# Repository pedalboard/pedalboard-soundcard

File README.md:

# Pedalboard Soundcard

I²S audio codec HAT for Raspberry Pi — ADC + DAC for the [Open Pedalboard](https://github.com/pedalboard) system.

**[Documentation →](https://pedalboard.github.io/pedalboard-soundcard/latest/)**

## Features

- TI Burr-Brown PCM1863 ADC (106dB SNR) + PCM5242 DAC (112dB SNR)
- Stereo differential input (guitar) + stereo output (amp)
- I²S interface to Raspberry Pi GPIO header
- Low-latency audio path for real-time effects
- Raspberry Pi HAT form factor

## Links

- [Interactive schematic & PCB viewer](https://pedalboard.github.io/pedalboard-soundcard/latest/board/)
- [Digi-Key shared list](https://www.digikey.ch/de/mylists/list/OT2O5ZLS9K)

## Development Setup

### Prerequisites

- [KiCad](https://www.kicad.org/) 10+
- [KiKit](https://github.com/yaqwsx/KiKit) (panelization)
- [mise](https://mise.jdx.dev/) (environment management)

### Environment

The schematic references KiKit's symbol and footprint libraries via the `${KIKIT_LIB}` environment variable. This is set per-machine using a `mise.local.toml` file (gitignored).

After cloning, create `mise.local.toml` in the project root:

```toml
[env]
KIKIT_LIB = "/path/to/kikit/resources"
```

Find your KiKit resources path with:

```sh
python3 -c "import kikit, os; print(os.path.join(os.path.dirname(kikit.__file__), 'resources'))"
```

Then trust the config:

```sh
mise trust mise.local.toml
```

### Checks

Run ERC and DRC:

```sh
make test
```

## Acknowledgements

Based on Dave Vandenbout's [RPi Hat Template](https://github.com/devbisme/RPi_Hat_Template).
Schematics derived from Jośe Fernando Moyano's [ZynADC](https://github.com/zynthian/zynthian-hw/tree/master/ZynADAC) ([CC BY-SA 4.0](https://creativecommons.org/licenses/by-sa/4.0/)).

## License

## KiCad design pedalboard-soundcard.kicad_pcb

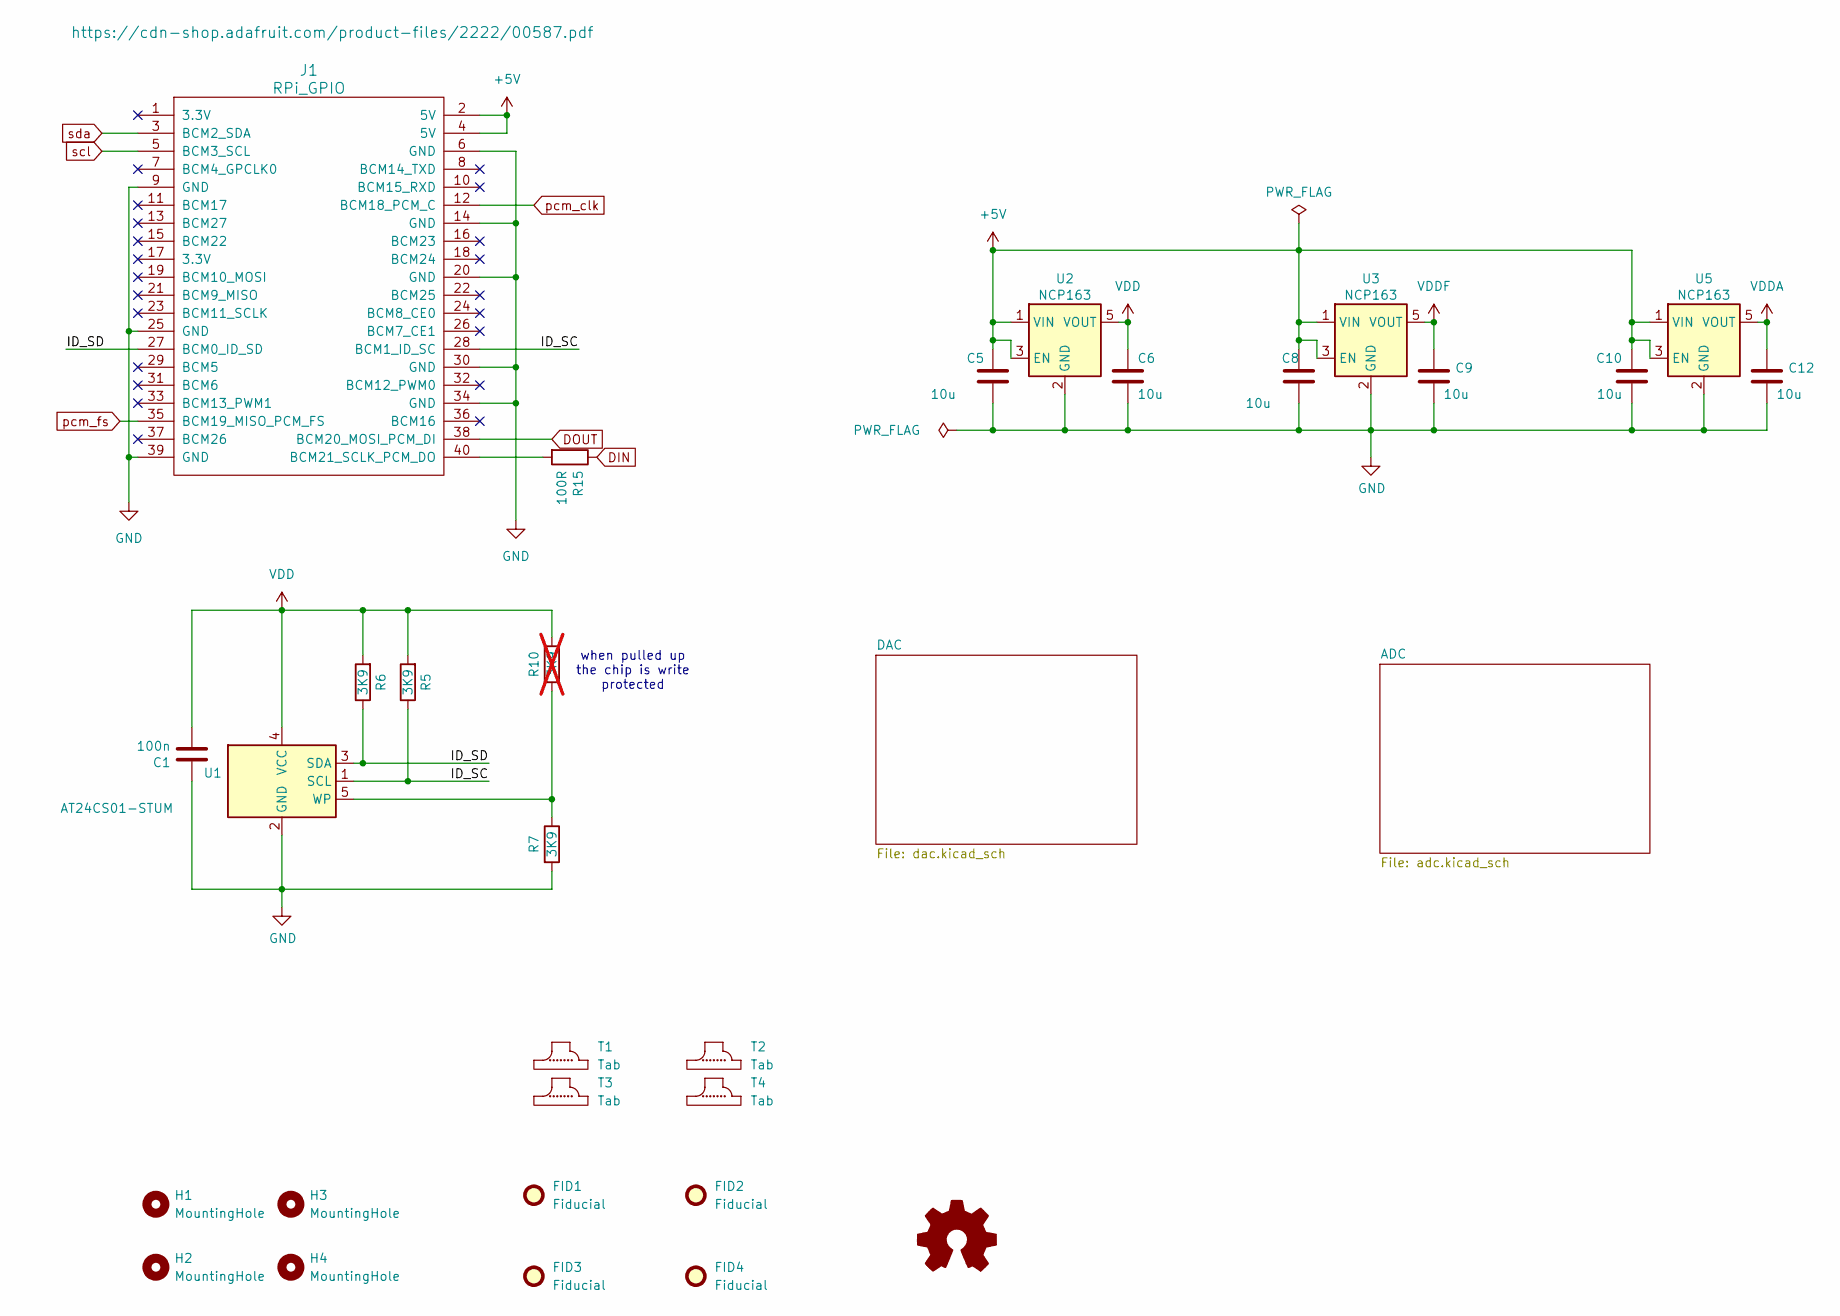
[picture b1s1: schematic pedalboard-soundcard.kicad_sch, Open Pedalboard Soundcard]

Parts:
C1: 100n; C_0805_2012Metric
C5, C6, C8, C9, C10, C12: 10u; C_0805_2012Metric
FID1, FID2, FID3, FID4: Fiducial; Fiducial_0.75mm_Mask1.5mm
H1, H2, H3, H4: MountingHole; RPi_Hat_Mounting_Hole
J1: RPi_GPIO; Pin_Header_Straight_2x20
R5, R6, R7: 3K9; R_0805_2012Metric
R10: 3K9; R_0805_2012Metric; not fitted
R15: 100R; R_0805_2012Metric
SYM1: Logo_Open_Hardware_Small; OSHW-Logo_5.7x6mm_SilkScreen
T1, T2, T3, T4: Tab
U1: AT24CS01-STUM; SOT-23-5
U2, U3, U5: NCP163; SOT-23-5

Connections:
+5V: C5.1, C8.1, C10.1, J1.2 (5V), J1.4 (5V), U2.1 (VIN), U2.3 (EN), U3.1 (VIN), U3.3 (EN), U5.1 (VIN), U5.3 (EN)
/ID_SC: J1.28 (BCM1_ID_SC), R5.1, U1.1 (SCL)
/ID_SD: J1.27 (BCM0_ID_SD), R6.1, U1.3 (SDA)
DIN: R15.1; also elsewhere on the board
DOUT: J1.38 (BCM20_MOSI_PCM_DI); also elsewhere on the board
GND: C1.1, C5.2, C6.2, C8.2, C9.2, C10.2, C12.2, J1.6 (GND), J1.9 (GND), J1.14 (GND), J1.20 (GND), J1.25 (GND), J1.30 (GND), J1.34 (GND), J1.39 (GND), R7.2, U1.2 (GND), U2.2 (GND), U3.2 (GND), U5.2 (GND); also elsewhere on the board
unnamed: J1.40 (BCM21_SCLK_PCM_DO), R15.2
unnamed: R7.1, R10.2, U1.5 (WP)
VDD: C1.2, C6.1, R5.2, R6.2, R10.1, U1.4 (VCC), U2.5 (VOUT); also elsewhere on the board
VDDA: C12.1, U5.5 (VOUT); also elsewhere on the board
VDDF: C9.1, U3.5 (VOUT); also elsewhere on the board
pcm_clk: J1.12 (BCM18_PCM_C); also elsewhere on the board
pcm_fs: J1.35 (BCM19_MISO_PCM_FS); also elsewhere on the board
scl: J1.5 (BCM3_SCL); also elsewhere on the board
sda: J1.3 (BCM2_SDA); also elsewhere on the board

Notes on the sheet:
when pulled up the chip is write protected

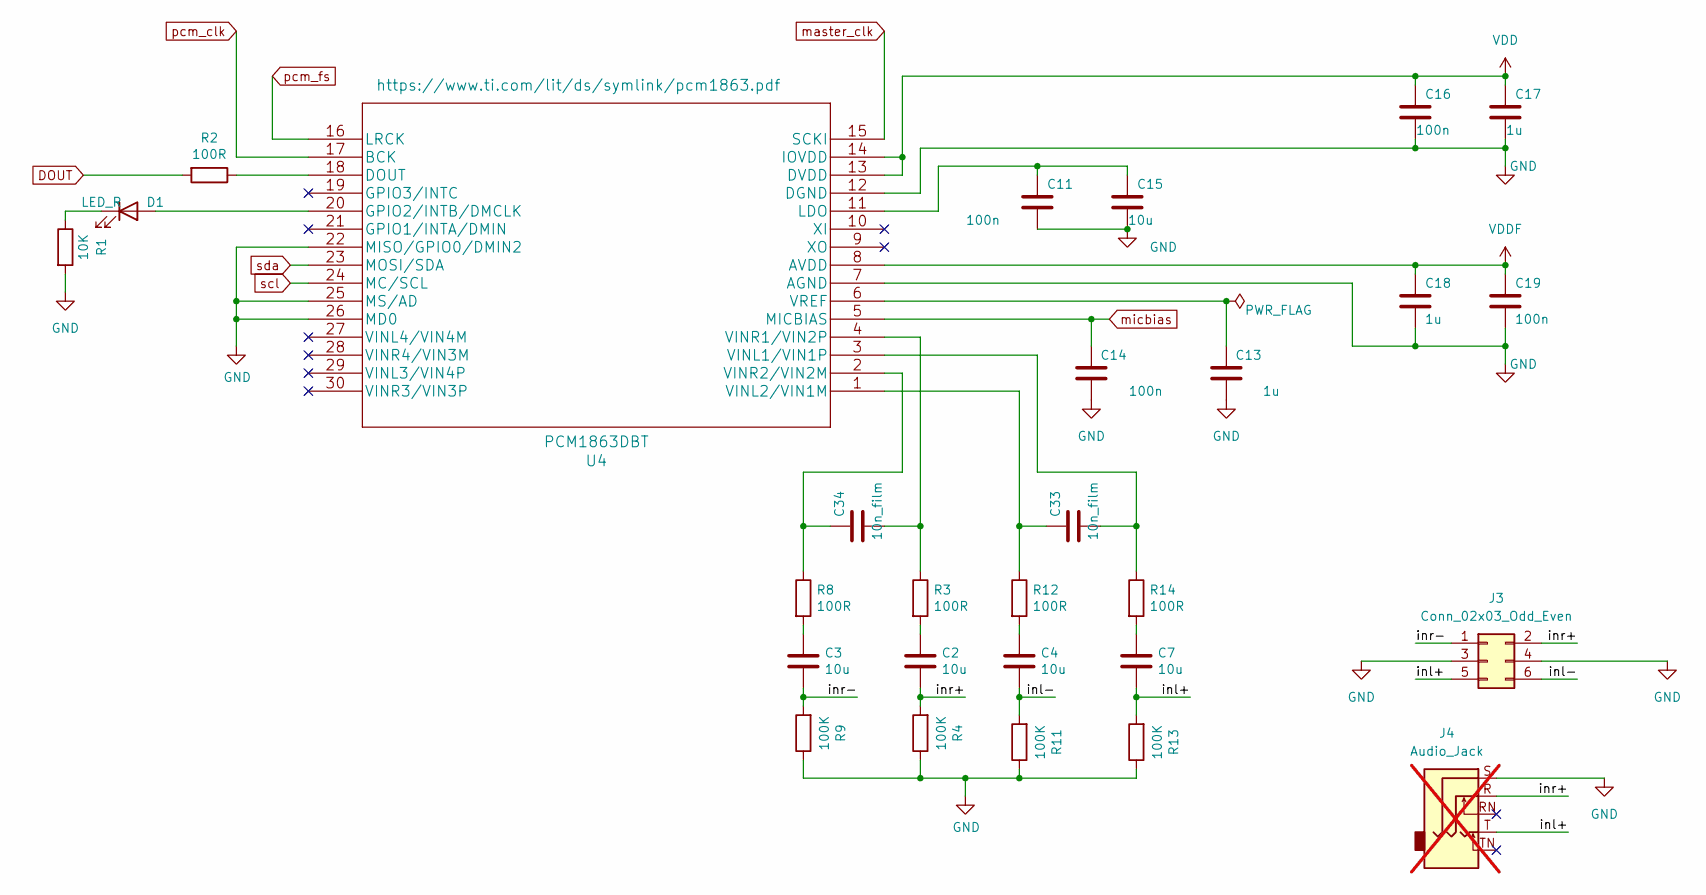
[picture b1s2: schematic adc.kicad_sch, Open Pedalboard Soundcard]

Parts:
C2, C3, C4, C7, C15: 10u; C_0805_2012Metric
C11, C14, C16, C19: 100n; C_0805_2012Metric
C13, C17, C18: 1u; C_0805_2012Metric
C33, C34: 10n_film; C_0805_2012Metric
D1: LED_R; LED_0805_2012Metric
J3: Conn_02x03_Odd_Even; PinSocket_2x03_P2.54mm_Vertical
J4: Audio_Jack; Jack_3.5mm_CUI_SJ1-3525N_Horizontal; not fitted
R1: 10K; R_0805_2012Metric
R2, R3, R8, R12, R14: 100R; R_0805_2012Metric
R4, R9, R11, R13: 100K; R_0805_2012Metric
U4: PCM1863DBT; TSSOP-30_4.4x7.8mm_P0.5mm

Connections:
/ADC/inl+: C7.2, J3.5, J4.T, R13.2
/ADC/inl-: C4.2, J3.6, R11.2
/ADC/inr+: C2.2, J3.2, J4.R, R4.2
/ADC/inr-: C3.2, J3.1, R9.2
DOUT: R2.2; also elsewhere on the board
GND: C11.2, C13.1, C14.1, C15.2, C16.2, C17.2, C18.2, C19.2, J3.3, J3.4, J4.S, R1.2, R4.1, R9.1, R11.1, R13.1, U4.7 (AGND), U4.12 (DGND), U4.22 (MISO/GPIO0/DMIN2), U4.25 (MS/AD), U4.26 (MD0); also elsewhere on the board
unnamed: C2.1, R3.2
unnamed: C3.1, R8.2
unnamed: C4.1, R12.2
unnamed: C7.1, R14.2
unnamed: D1.2 (A), U4.20 (GPIO2/INTB/DMCLK)
unnamed: D1.1 (K), R1.1
unnamed: R2.1, U4.18 (DOUT)
unnamed: C11.1, C15.1, U4.11 (LDO)
unnamed: C33.1, R14.1, U4.3 (VINL1/VIN1P)
unnamed: C33.2, R12.1, U4.1 (VINL2/VIN1M)
unnamed: C34.1, R3.1, U4.4 (VINR1/VIN2P)
unnamed: C34.2, R8.1, U4.2 (VINR2/VIN2M)
unnamed: C13.2, U4.6 (VREF)
VDD: C16.1, C17.1, U4.13 (DVDD), U4.14 (IOVDD); also elsewhere on the board
VDDF: C18.1, C19.1, U4.8 (AVDD); also elsewhere on the board
master_clk: U4.15 (SCKI); also elsewhere on the board
micbias: C14.2, U4.5 (MICBIAS)
pcm_clk: U4.17 (BCK); also elsewhere on the board
pcm_fs: U4.16 (LRCK); also elsewhere on the board
scl: U4.24 (MC/SCL); also elsewhere on the board
sda: U4.23 (MOSI/SDA); also elsewhere on the board

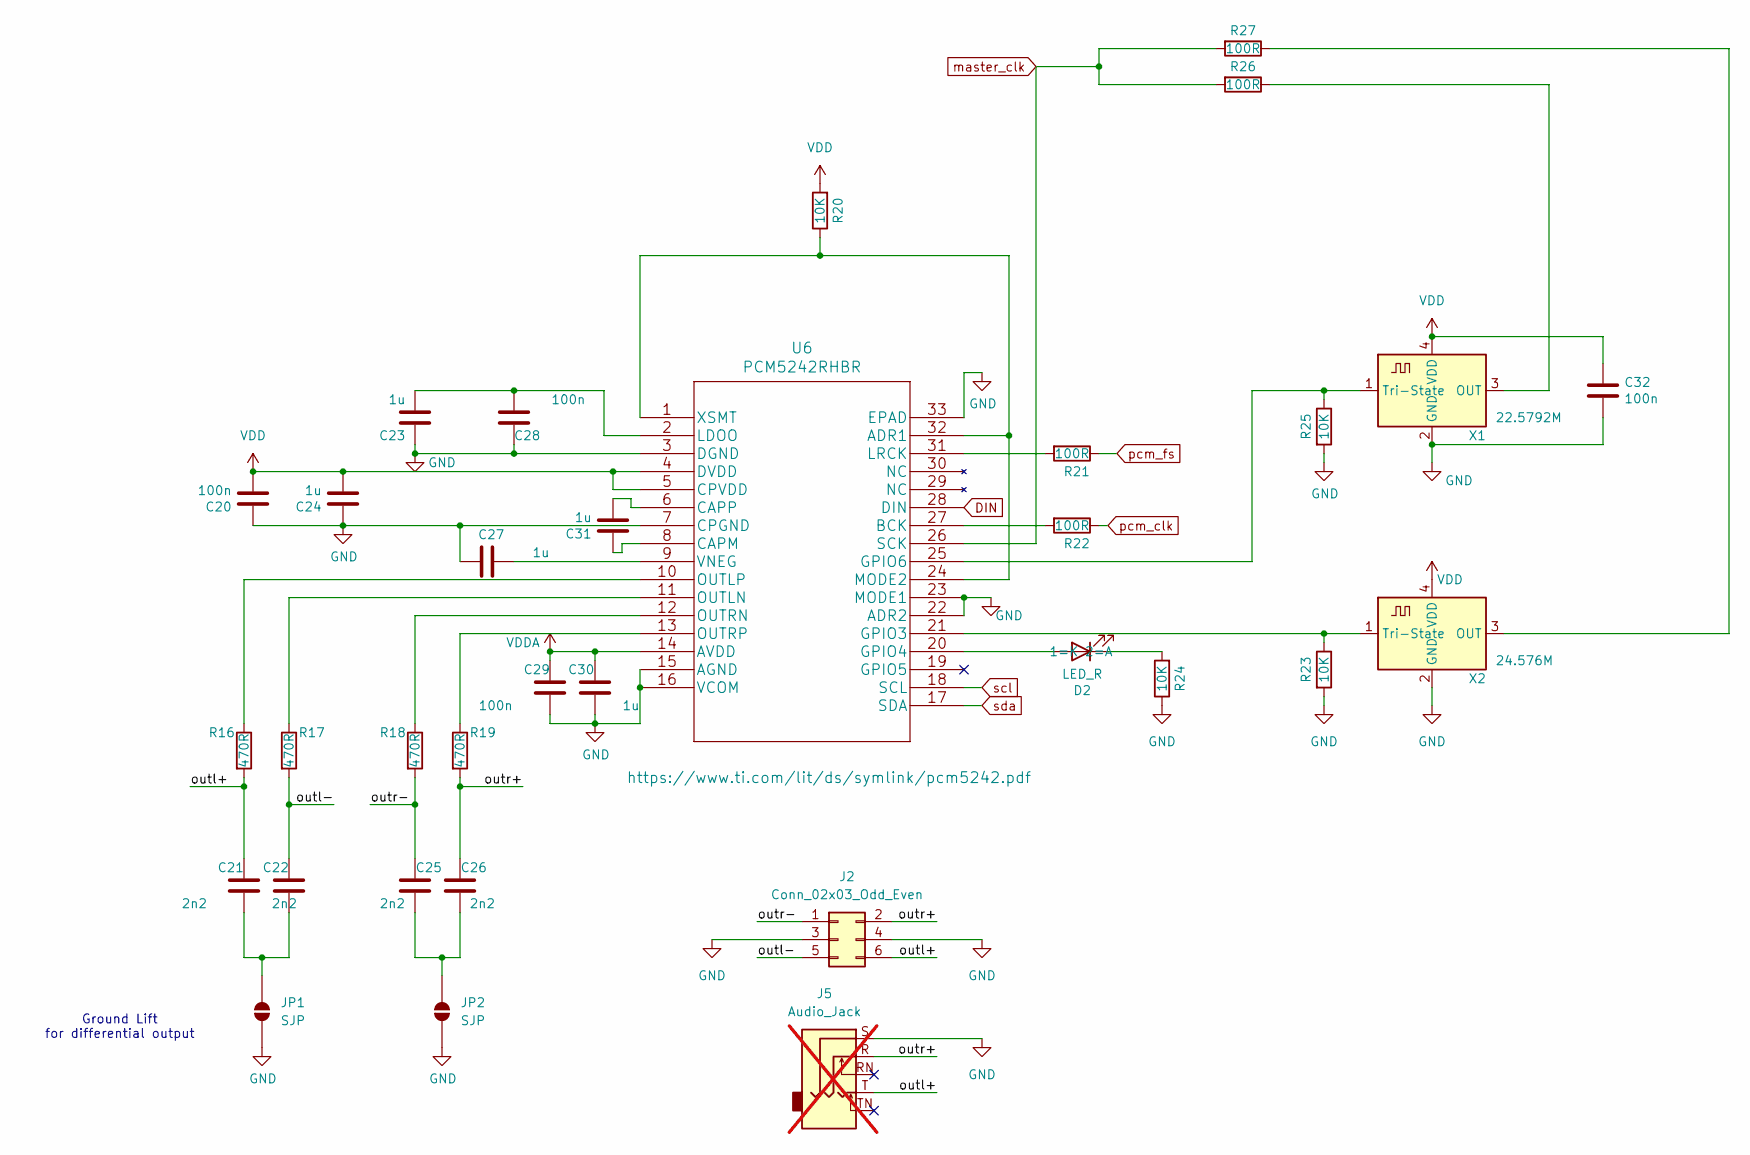
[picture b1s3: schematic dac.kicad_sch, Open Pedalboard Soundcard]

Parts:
C20, C28, C29, C32: 100n; C_0805_2012Metric
C21, C22, C25, C26: 2n2; C_0805_2012Metric
C23, C24, C27, C30, C31: 1u; C_0805_2012Metric
D2: LED_R; LED_0805_2012Metric
J2: Conn_02x03_Odd_Even; PinSocket_2x03_P2.54mm_Vertical
J5: Audio_Jack; Jack_3.5mm_CUI_SJ1-3525N_Horizontal; not fitted
JP1, JP2: SJP
R16, R17, R18, R19: 470R; R_0805_2012Metric
R20, R23, R24, R25: 10K; R_0805_2012Metric
R21, R22, R26, R27: 100R; R_0805_2012Metric
U6: PCM5242RHBR; HVQFN-32-1EP_5x5mm_P0.5mm_EP3.1x3.1mm_ThermalVias
X1: 22.5792M; Oscillator_SMD_Abracon_ASDMB-4Pin_2.5x2.0mm
X2: 24.576M; Oscillator_SMD_Abracon_ASDMB-4Pin_2.5x2.0mm

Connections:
/DAC/outl+: C21.1, J2.6, J5.T, R16.2
/DAC/outl-: C22.1, J2.5, R17.2
/DAC/outr+: C26.1, J2.2, J5.R, R19.2
/DAC/outr-: C25.1, J2.1, R18.2
DIN: U6.28 (DIN); also elsewhere on the board
GND: C20.1, C23.1, C24.1, C27.1, C28.1, C29.2, C30.1, C32.2, J2.3, J2.4, J5.S, JP1.1 (A), JP2.1 (A), R23.2, R24.1, R25.2, U6.3 (DGND), U6.7 (CPGND), U6.15 (AGND), U6.16 (VCOM), U6.22 (ADR2), U6.23 (MODE1), U6.33 (EPAD), X1.2 (GND), X2.2 (GND); also elsewhere on the board
unnamed: D2.2 (A), U6.20 (GPIO4)
unnamed: D2.1 (K), R24.2
unnamed: C21.2, C22.2, JP1.2 (B)
unnamed: C25.2, C26.2, JP2.2 (B)
unnamed: R20.1, U6.1 (XSMT), U6.24 (MODE2), U6.32 (ADR1)
unnamed: R22.2, U6.27 (BCK)
unnamed: C31.1, U6.8 (CAPM)
unnamed: C31.2, U6.6 (CAPP)
unnamed: R23.1, U6.21 (GPIO3), X2.1 (Tri-State)
unnamed: R25.1, U6.25 (GPIO6), X1.1 (Tri-State)
unnamed: C23.2, C28.2, U6.2 (LDOO)
unnamed: R21.2, U6.31 (LRCK)
unnamed: R17.1, U6.11 (OUTLN)
unnamed: R16.1, U6.10 (OUTLP)
unnamed: R18.1, U6.12 (OUTRN)
unnamed: R19.1, U6.13 (OUTRP)
unnamed: C27.2, U6.9 (VNEG)
unnamed: R26.1, X1.3 (OUT)
unnamed: R27.1, X2.3 (OUT)
VDD: C20.2, C24.2, C32.1, R20.2, U6.4 (DVDD), U6.5 (CPVDD), X1.4 (VDD), X2.4 (VDD); also elsewhere on the board
VDDA: C29.1, C30.2, U6.14 (AVDD); also elsewhere on the board
master_clk: R26.2, R27.2, U6.26 (SCK); also elsewhere on the board
pcm_clk: R22.1; also elsewhere on the board
pcm_fs: R21.1; also elsewhere on the board
scl: U6.18 (SCL); also elsewhere on the board
sda: U6.17 (SDA); also elsewhere on the board

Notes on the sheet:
Ground Lift for differential output

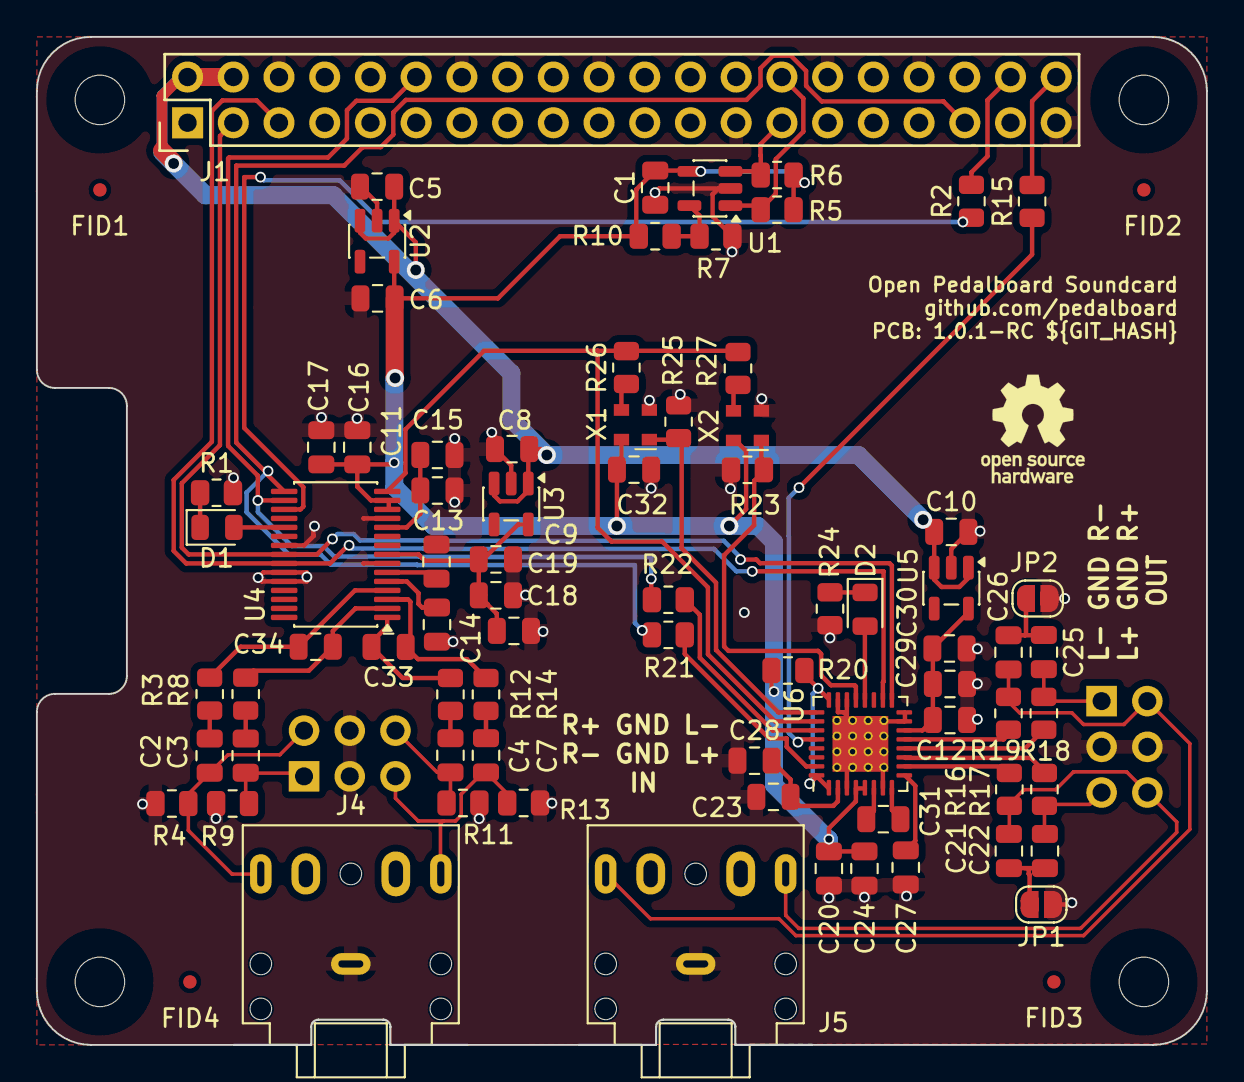
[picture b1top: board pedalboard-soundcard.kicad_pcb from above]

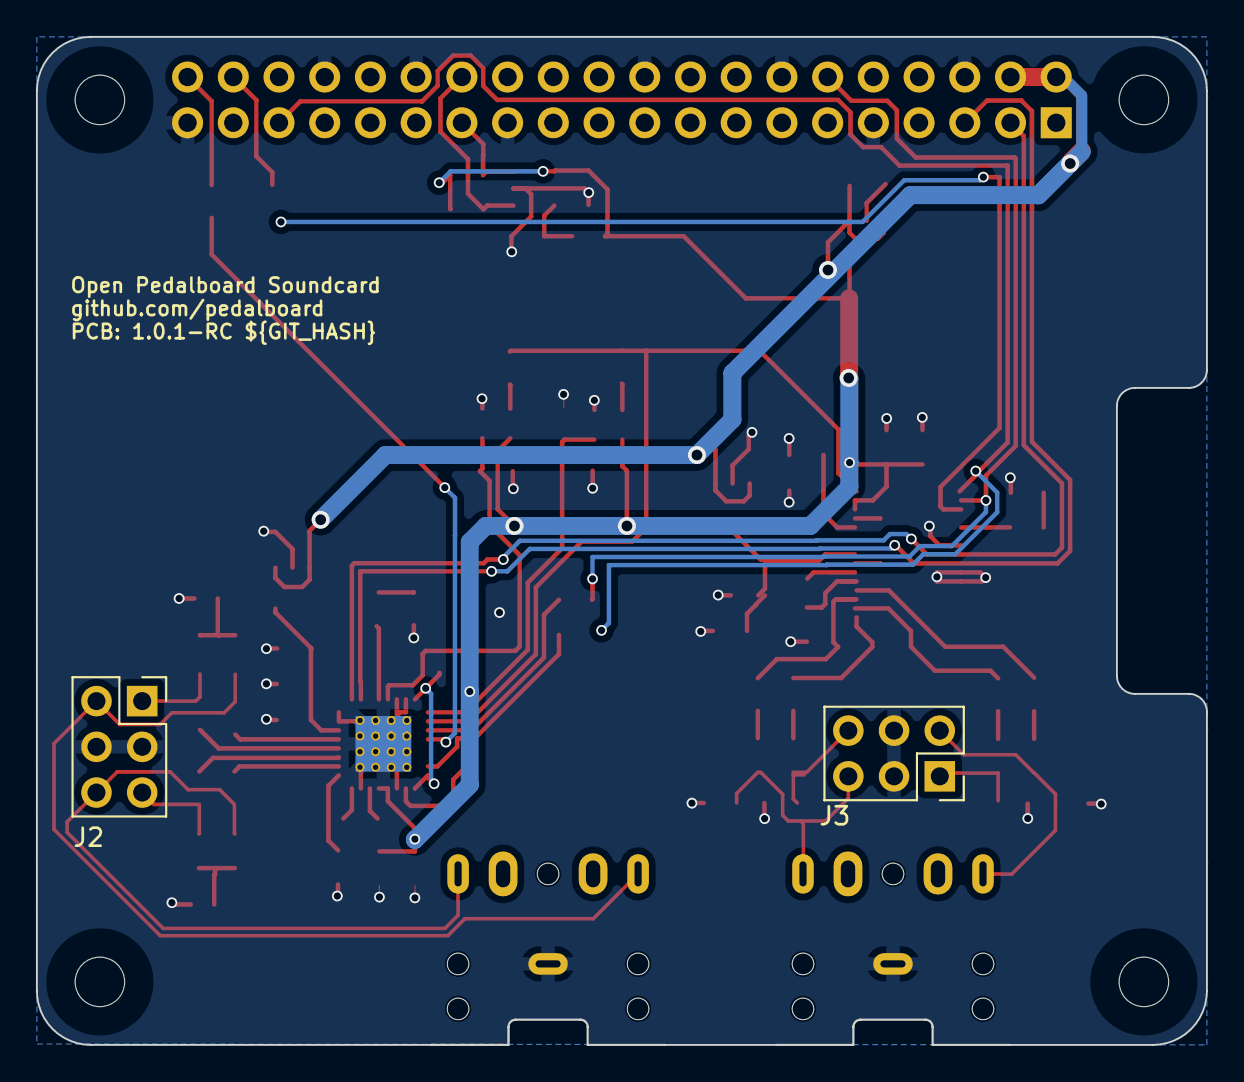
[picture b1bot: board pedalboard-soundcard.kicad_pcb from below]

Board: 2 copper layers, 65.0 x 56.0 mm, 91 parts (2 on the bottom side), 57 nets.

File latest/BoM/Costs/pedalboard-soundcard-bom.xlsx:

|  | KiBot Bill of Materials
 |  | Schematic: | pedalboard-soundcard | Component Groups: | 21
 |  | Variant: | default | Component Count: | 76 (71 SMD/ 5 THT)
 |  | Revision: | 1.0.1-RC | Fitted Components: | 73 (70 SMD/ 3 THT)
 |  | Date: | 2024-10-16 | Number of PCBs: | 1
 |  | KiCad Version: | 9.0.7+1 | Total Components: | 73
Row | Description | Part | References | Value | Footprint | Quantity Per PCB | Status | Datasheet | Supplier | Sim.Pins
1 |  | C | C21 C22 C25 C26 | 2n2 | C_0805_2012Metric | 4 |  | https://www.samsungsem.com/resources/file/global/support/pro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 | https://www.digikey.ch/de/products/detail/samsung-electro-me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
2 |  | C | C33 C34 | 10n_film | C_0805_2012Metric | 2 |  | https://industrial.panasonic.com/ww/products/pt/film-cap-ele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 | https://www.digikey.ch/en/products/detail/panasonic-electron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
3 |  | C | C1 C11 C14 C16 C19 C20 C28 C29 C32 | 100n | C_0805_2012Metric | 9 |  | https://www.samsungsem.com/resources/file/global/support/pro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 | https://www.digikey.ch/de/products/detail/samsung-electro-me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
4 |  | C | C13 C17 C18 C23 C24 C27 C30 C31 | 1u | C_0805_2012Metric | 8 |  | https://www.samsungsem.com/resources/file/global/support/pro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 | https://www.digikey.ch/de/products/detail/samsung-electro-me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
5 |  | C | C2 C3 C4 C5 C6 C7 C8 C9 C10 C12 C15 | 10u | C_0805_2012Metric | 11 |  | https://www.samsungsem.com/resources/file/global/support/pro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 | https://www.digikey.ch/de/products/detail/samsung-electro-me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
6 |  | LED | D1 D2 | LED_R | LED_0805_2012Metric | 2 |  | ~ |  | 1=K 2=A
7 |  | Conn_02x03_Odd_Even | J2 J3 | Conn_02x03_Odd_Even | PinSocket_2x03_P2.54mm_Vertical | 2 |  | https://www.te.com/commerce/DocumentDelivery/DDEController?A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 | https://www.digikey.ch/de/products/detail/te-connectivity-am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
8 |  | RPi_GPIO | J1 | RPi_GPIO | Pin_Header_Straight_2x20 | 1 |  | https://cdn-shop.adafruit.com/product-files/2222/00587.pdf | https://www.digikey.ch/en/products/detail/adafruit-industrie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
9 |  | R | R2 R3 R8 R12 R14 R15 R21 R22 R26 R27 | 100R | R_0805_2012Metric | 10 |  | https://www.seielect.com/catalog/sei-rmcf_rmcp.pdf | https://www.digikey.ch/de/products/detail/stackpole-electron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
10 |  | R | R16 R17 R18 R19 | 470R | R_0805_2012Metric | 4 |  | https://www.seielect.com/catalog/sei-rmcf_rmcp.pdf | https://www.digikey.ch/de/products/detail/stackpole-electron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
11 |  | R | R5 R6 R7 | 3K9 | R_0805_2012Metric | 3 |  | https://www.seielect.com/catalog/sei-rmcf_rmcp.pdf | https://www.digikey.ch/de/products/detail/stackpole-electron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
12 |  | R | R1 R20 R23 R24 R25 | 10K | R_0805_2012Metric | 5 |  | https://www.seielect.com/catalog/sei-rmcf_rmcp.pdf | https://www.digikey.ch/de/products/detail/stackpole-electron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
13 |  | R | R4 R9 R11 R13 | 100K | R_0805_2012Metric | 4 |  | https://www.seielect.com/catalog/sei-rmcf_rmcp.pdf | https://www.digikey.ch/de/products/detail/stackpole-electron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
14 |  | AT24CS01-STUM | U1 | AT24CS01-STUM | SOT-23-5 | 1 |  | https://ww1.microchip.com/downloads/en/DeviceDoc/AT24C01C-AT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 | https://www.digikey.ch/de/products/detail/microchip-technolo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
15 |  | NCP163ASN330T1G | U2 U3 U5 | NCP163 | SOT-23-5 | 3 |  | https://www.onsemi.com/pdf/datasheet/ncp163-d.pdf | https://www.digikey.ch/de/products/detail/onsemi/NCP163ASN33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
16 |  | PCM1863DBT-pcm1863 | U4 | PCM1863DBT | TSSOP-30_4.4x7.8mm_P0.5mm | 1 |  | https://www.ti.com/lit/ds/symlink/pcm1863.pdf | https://www.digikey.ch/de/products/detail/texas-instruments/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
17 |  | PCM5242RHBR-pcm5242 | U6 | PCM5242RHBR | HVQFN-32-1EP_5x5mm_P0.5mm_EP3.1x3.1mm_ThermalVias | 1 |  | https://www.ti.com/lit/ds/symlink/pcm5242.pdf | https://www.digikey.ch/de/products/detail/texas-instruments/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
18 |  | ASCO-Oscillator | X1 | 22.5792M | Oscillator_SMD_Abracon_ASDMB-4Pin_2.5x2.0mm | 1 |  | https://media.digikey.com/pdf/Data%20Sheets/Kyocera%20Intern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 | https://www.digikey.ch/en/products/detail/kyocera-avx/KC2016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
19 |  | ASCO-Oscillator | X2 | 24.576M | Oscillator_SMD_Abracon_ASDMB-4Pin_2.5x2.0mm | 1 |  | https://media.digikey.com/pdf/Data%20Sheets/Kyocera%20Intern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 | https://www.digikey.ch/en/products/detail/kyocera-avx/KC2016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

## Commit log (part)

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2023-12-12 Initial revision
2023-12-19 First placement of parts on PCB
2023-12-19 Add build system
2023-12-19 Add credits to the schema sources
2023-12-19 Fix pipeline
2023-12-19 Add link to docs
2023-12-19 Page settings
2023-12-22 Distribute parts on PCB
2023-12-23 First routing attempt
2023-12-23 Cleanup routing
2023-12-23 Releave the rules
2023-12-23 Fix 40pin connector silkscreen
2023-12-23 Add link to generated docs
2023-12-23 Fix 3d views
2023-12-23 Use blender views
2023-12-23 Improve 3d model
2023-12-23 Improve 3d models (XTAL)
2023-12-23 Cleanup placement
2023-12-23 Minimum 0.3mm holes
2023-12-23 Dicrease material thickness
2023-12-23 Improve dimenstions
2023-12-23 Cleanup silkscreen
2023-12-23 Link for release procedure
2023-12-23 PCB text
2023-12-26 improve BOM
2023-12-26 Fix ibom link
2023-12-26 Update from schematics
2023-12-27 Cleanup schematic for eeprom
2023-12-27 Replace 5v global label with +5V power
2023-12-27 Replace DVDD global label with VDD power symbol
2023-12-27 Use VDD symbol instead of lines
2023-12-27 Use more Power symbols
2023-12-27 Simplify/cleanup schematic
2023-12-27 Improve readability of schematics
2023-12-27 Cleanup schematics again
2023-12-27 Use Power Symbols for analog power
2023-12-27 Add Fiducials and OSHW logo
2023-12-27 Smaller OSHW Logo
2023-12-27 Add texts for connectors
2023-12-27 Revert to standard RPI headers
2023-12-27 Fix reverted connectors
2023-12-27 Fix library
2023-12-27 Add CHANGELOG.md
2023-12-28 Fix libary table
2023-12-28 Add 3.5mm jack connectors
2023-12-28 DNP 3.5mm jack connectors
2023-12-28 Add digikey shared list
2024-01-07 Add TODO
2024-01-07 Enable DRC
2024-01-07 Try drc exclusion workaround
2024-01-07 Add git commit to schema sheets and PCB sheet
2024-01-07 Fix CHANGELOG
2024-01-07 Silkscreen cleanup
2024-01-07 PCB ID also on B.Silkscreen
2024-03-10 Add first paneliyse config file incl. Makefile target to test locally
2024-03-12 Add panel output to kibot
2024-03-12 Fix panlel output
2024-03-12 Temporarly disable drc
2024-03-12 fix syntax
2024-03-12 Fix panlel syntax again
2024-03-12 (try to) Fix panlel syntax
2024-03-12 Add panel tabs
2024-03-12 Add tooling and fiducials to frame
2024-03-12 Add post processing
2024-10-04 Use latest download artifacts version
2024-10-04 Use latest upload artifacts version
2024-10-04 Use checkout v4 action
2024-10-04 Use checkout v4 deply action
2024-10-04 Upgrade to v8
2024-10-04 3d zoom change
2024-10-14 DNP for pull up
2024-10-14 Ground Lift for differential output
2024-10-15 Add makefile targets
2024-10-15 Use ascii format
2024-10-16 Fix errors and warnings
2024-10-16 Update footprints
2024-10-16 Fix warnings. Add input capacitor
2024-10-16 Exclude temporarly
2024-10-16 Bump version to 1.0.0
2024-10-16 Bump version to 1.0.1-RC
2024-10-17 Improve Makefile (custom bom)
2024-10-31 Add bom2inventree script
2024-12-15 Add first pnp job
2024-12-15 Setup OpenPNP
2024-12-15 Align LED value with other projects
2024-12-15 Update the oscilator part definitions
2024-12-15 Update jig size
2024-12-15 Simpler git version
2024-12-15 Fix all DRC errors
2024-12-15 Enable erc/drc
2024-12-16 Replace deprecated parameter
2024-12-23 TODOs added for next version
2025-04-21 Schema: Update to kicad v9
2025-04-21 PCB: Update to kicad v9
2025-04-21 kibot upgrade to v9
2025-04-21 Changelog
2025-04-21 Update from schema
2025-04-21 Refert to latest docs
2025-04-30 Fix pnp pcb hight
2025-05-02 Add TODOs
2025-05-02 Add pnp feeder config
2025-06-01 Add eeprom settings
2026-04-14 Deploy to gh-pages branch with version picker
    - Replace cross-repo deploy with gh-pages in same repo
    - Add version picker landing page
    - Tag-triggered versioned deploy
    - Update README URLs
2026-04-14 Initial gh-pages commit
2026-04-14 Deploying to gh-pages from @ pedalboard/pedalboard-soundcard@d2231e45027aa9442ba1dd8e33bf3cecee7856a0 🚀
2026-04-14 Fix GitHub repo link
2026-04-14 Deploying to gh-pages from @ pedalboard/pedalboard-soundcard@ae131ea72ef5b690fe7eef351c5c9c46a6d1ebfc 🚀
2026-04-17 switch to hugo-kicad-site theme
    Replaces custom landing page and CI with the reusable Hugo theme.
    Board page (KiCanvas + gallery + iBOM), release page (downloads + diffs).
2026-04-17 reset versions.json for new theme
2026-04-17 Deploying to gh-pages from @ pedalboard/pedalboard-soundcard@1ae303df43f3f71039cf5756ff3d9059f2a3788b 🚀
2026-04-18 clean latest/ for fresh Hugo deploy
2026-04-18 trigger rebuild (clean gh-pages)
2026-04-18 trigger CI rebuild
2026-04-18 Deploying to gh-pages from @ pedalboard/pedalboard-soundcard@06fd434fb560ce3346101827bfdc8df8dd2a6862 🚀
2026-04-18 trigger rebuild (fix KiBot index.html override)
2026-04-18 Deploying to gh-pages from @ pedalboard/pedalboard-soundcard@7072a3c5f8963443bbf12f59d9cafb49c243a5c3 🚀
2026-04-18 add v1.0.0 link to old site
2026-04-18 trigger rebuild (version picker external URL support)
2026-04-18 add 3D render to overview page
2026-04-18 kibot: disable basic 3D renders (Blender renders are sufficient)
2026-04-18 Deploying to gh-pages from @ pedalboard/pedalboard-soundcard@778cbdf669e4cbb4509d077c05912a7dd4d1a7d5 🚀
2026-04-18 Deploying to gh-pages from @ pedalboard/pedalboard-soundcard@d8f0571ec10daa6eb208d9ed63dabf2112240391 🚀
2026-04-18 Deploying to gh-pages from @ pedalboard/pedalboard-soundcard@f55275aeb06701d830970d621876adc70fedc67b 🚀
2026-04-18 update README: link to Hugo doc site
2026-04-18 overview: add audio specs (PCM1863/PCM5242)
2026-04-18 Deploying to gh-pages from @ pedalboard/pedalboard-soundcard@4db171267a710117d24145f93e8d6e4bbe2fde26 🚀
2026-04-18 overview: add license badge
2026-04-18 Deploying to gh-pages from @ pedalboard/pedalboard-soundcard@f3118fb8e7f68d3d9220c6f118cc43a7d92ddad2 🚀
2026-04-18 remove redundant badge from overview (now in footer)
2026-04-18 Deploying to gh-pages from @ pedalboard/pedalboard-soundcard@17e4ebfa839173b9c55ebce373a518f870c9eeb5 🚀
2026-04-18 overview: cross-link related boards
2026-04-18 README: add audio specs, consistent structure
2026-04-18 Deploying to gh-pages from @ pedalboard/pedalboard-soundcard@d6b9adea21de15f627e8d3f7a7656a2aa6298150 🚀
2026-04-21 site: add .mise.toml, update theme vendor (hugo-kicad-site v1.0.3)
2026-04-21 ci: switch to KiCad 10 container with kicad-packages3d
2026-04-21 Deploying to gh-pages from @ pedalboard/pedalboard-soundcard@5cc322b5200872b3657637b5854c8fd7ecdfa751 🚀
2026-04-21 ci: remove kibot_install (3D models now cached by workflow)
2026-04-22 Add KiKit library setup via mise environment variable
2026-04-22 Migrate to KiCad 10 file format
2026-04-22 Update footprints from library and adjust DRC severity settings
2026-04-22 Fix solder jumper footprint references and parity issues
2026-04-22 Gitignore local artifacts (KiCad history, Hugo build lock, site static)
2026-04-22 Remove HPGL outputs (discontinued in KiCad 10)
2026-04-22 Update changelog for KiCad 10 migration
2026-04-22 Remove pcbdraw, render_3d and kikit_present outputs (keep Blender only)
2026-04-22 Deploying to gh-pages from @ pedalboard/pedalboard-soundcard@cfda140f203ccbfb31539b21b99655dfad127fb0 🚀
2026-04-22 Deploying to gh-pages from @ pedalboard/pedalboard-soundcard@95a273a64299cf2b04a6bcd4cb679e8c689c30cb 🚀
2026-04-22 Add default text variables for title block (GIT_HASH, REVISION)
2026-04-22 Install kicad-packages3d for Blender 3D export in CI
2026-04-22 Deploying to gh-pages from @ pedalboard/pedalboard-soundcard@80062617507ac7933be18997dff7502358ed753e 🚀
2026-04-22 Trigger rebuild (KICAD10_3DMODEL_DIR fix in reusable workflow)
2026-04-22 Align Blender render config with granit (lighting, perspectives)
2026-04-22 Align Blender render config with granit (lighting, perspectives, filenames)
2026-04-22 Deploying to gh-pages from @ pedalboard/pedalboard-soundcard@b651fcc4d9002e7f3acbf86250d468447af45510 🚀
2026-04-22 Deploying to gh-pages from @ pedalboard/pedalboard-soundcard@31afb6017ae6b522b8181885fa29b64f5e88adff 🚀
2026-04-22 Remove kibot_install and container_image (now defaults in reusable workflow)
2026-04-22 Deploying to gh-pages from @ pedalboard/pedalboard-soundcard@121d40d3377e59054d80a3f7628d9cd9ecaca75b 🚀
2026-04-22 Increase Blender render resolution to 4K (3840x2160)
2026-04-22 Deploying to gh-pages from @ pedalboard/pedalboard-soundcard@14fb67eb2d38b9647849726f6b280fd76ecebb48 🚀
2026-04-22 Reduce Blender render resolution to QHD (2560x1440)
2026-04-22 Deploying to gh-pages from @ pedalboard/pedalboard-soundcard@79b93a2f33fa6b0a9f04401e093466d9327aae09 🚀
2026-04-22 Update hugo-kicad-site theme to latest main
2026-04-22 Deploying to gh-pages from @ pedalboard/pedalboard-soundcard@43ae5f7f469564ff0b28db6c3b510184d9688de4 🚀
2026-04-23 Add GitHub icon to header menu link
2026-04-23 Deploying to gh-pages from @ pedalboard/pedalboard-soundcard@0fbefd4712494fc8b462237da822dc83822148ea 🚀
2026-05-06 Migrate site theme to Hextra (v1.1.0)
2026-05-06 Deploying to gh-pages from @ pedalboard/pedalboard-soundcard@77f580b22c44a5be41898fd2f4921ac181a39a88 🚀
2026-05-12 Deploying to gh-pages from @ pedalboard/pedalboard-soundcard@b920d0f60fa750fc830212c47e7f0d8dba3abd35 🚀
2026-05-13 Remove _vendor directory (use Hugo module resolution)
2026-05-13 Deploying to gh-pages from @ pedalboard/pedalboard-soundcard@dc562330052bb9dca7300b94083724d9ba66bf31 🚀

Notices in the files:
README.md:
[License: CERN-OHL-P-2.0](LICENSE.txt)
adc.kicad_sch:
License: CERN Open Hardware Licence Version 2 - Permissive
